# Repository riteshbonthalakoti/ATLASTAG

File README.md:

# AtlasTag

> **AtlasTag** is an ultra-compact, long-battery-life hardware asset-tracking platform combining GNSS satellite positioning, cellular IoT connectivity (LTE-M / NB-IoT), motion-triggered intelligence, and local fail-safe telemetry storage. Developed for **Hack Club Half Life**.

---

## Concept & Vision Reel

> [!NOTE]
> **Idea & Concept Showcase:** This video is an **idea reel / conceptual mockup** visualizing the intended asset-tracking experience, compact form-factor goals, and operational scenario for AtlasTag. It illustrates the project goals rather than physical bench-tested hardware (hardware design and subsystem validation are currently underway in Week 1).

https://github.com/user-attachments/assets/558ffe17-422e-43a5-9f9e-540db29d0795

---

## The Problem & The AtlasTag Approach

Most popular asset trackers (such as Apple AirTags or Tile) rely exclusively on crowd-sourced Bluetooth networks. When an asset leaves urban density or moves along transit highways, rural routes, or industrial yards without nearby smartphones, **tracking is lost**.

AtlasTag is engineered to operate **fully autonomously**:
- **Direct Satellite Positioning:** Acquires real-world geographic coordinates via multi-constellation GNSS (GPS, GLONASS, Galileo, BeiDou) without relying on external devices.
- **Direct Cellular Telemetry:** Transmits location packets directly to cloud servers over power-efficient LTE-M or NB-IoT networks.
- **Fail-Safe Offline Storage:** When traversing cellular dead zones or shielded containers, telemetry records are queued in local SPI NOR Flash memory and uploaded automatically once coverage is restored.
- **Ultra-Low Power Motion Gating:** Stays in deep micro-ampere sleep when stationary, waking up instantaneously via accelerometer interrupts when motion or tampering is detected.

---

## Visual Architecture & Data Flow

```mermaid
flowchart LR
    %% Main Pipeline
    Motion["🚶 Motion Sensor<br/><b>(Detects Movement)</b>"]
    -->|"1. Hardware Interrupt"| Brain["🧠 Host MCU / Controller<br/><b>(System Logic)</b>"]

    GPS["🛰️ GNSS Satellites<br/><b>(Latitude / Longitude)</b>"]
    -->|"2. Position Fix"| Brain

    Brain
    -->|"3. Formats Packet"| Modem["📶 Cellular Modem<br/><b>(LTE-M / NB-IoT)</b>"]

    Modem
    -->|"4. Cloud Uplink"| CloudApp["📱 Web / Mobile App<br/><b>(Live Map & Alerts)</b>"]

    %% Backup Storage
    Modem -.->|"No Signal (Offline)"| Storage["💾 SPI NOR Flash<br/><b>(Queues Telemetry)</b>"]
    Storage -.->|"Burst Upload on Reconnect"| Modem

    %% Power
    Power["🔋 Li-Po Battery & Charger<br/><b>(Power Management)</b>"]
    ==>|"Regulated 3.3V & VBAT Burst"| Brain

    %% Styling
    style Motion fill:#E8F5E9,stroke:#2E7D32,stroke-width:2px,color:#1B5E20
    style GPS fill:#E1F5FE,stroke:#0288D1,stroke-width:2px,color:#01579b
    style Brain fill:#EDE7F6,stroke:#512DA8,stroke-width:2px,color:#311B92
    style Modem fill:#FFF3E0,stroke:#E65100,stroke-width:2px,color:#BF360C
    style CloudApp fill:#FCE4EC,stroke:#C2185B,stroke-width:2px,color:#880E4F
    style Storage fill:#FFFDE7,stroke:#FBC02D,stroke-width:2px,color:#F57F17
    style Power fill:#ECEFF1,stroke:#455A64,stroke-width:2px,color:#263238
```

### The 5-Step Operating Cycle

1. **Deep Sleep Preservation:** Between tracking events, the system enters deep sleep, turning off RF radios to maximize battery longevity.
2. **Motion-Triggered Wakeup:** When vibration or acceleration exceeds the programmed threshold, the low-power accelerometer asserts a hardware interrupt pin to wake the host controller.
3. **Satellite GNSS Fix:** The GNSS receiver powers on, locks ephemeris data, and acquires high-accuracy geographic coordinates.
4. **Cellular Uplink:** The cellular engine establishes an LTE-M / NB-IoT network bearer and pushes the telemetry packet to the endpoint.
5. **Store-and-Forward Safety Net:** If no cellular tower acknowledges transmission, the packet is written to the on-board Winbond SPI Flash queue and forwarded during the next successful network attachment.

---

## Current Status: Week 1 Modular Baseboard

*AtlasTag Week 1 Modular Prototype Baseboard (45 × 35 mm, 4-Layer Controlled-Impedance Stackup).*

### Current Engineering State:
- **Schematic Capture Complete:** Authoritative baseboard schematic captured in KiCad 10.0.6 (`hardware/kicad/atlastag.kicad_sch`), passing electrical rules check (ERC) with zero critical errors.
- **Modular Mezzanine Architecture:** Implements a standardized 16-pin interface (VBAT, 3.3V, GND, UART, control GPIOs, SIM interface), keeping the Cellular/GNSS modem selection **open** and avoiding unverified fine-pitch BGA/LGA soldering risks.
- **Power Path Design:**
  - **USB-C Interface:** Mid-mount receptacle with dual 5.1 kΩ CC pull-downs for standard 5V supply negotiation.
  - **Battery Charger:** Microchip MCP73831 linear Li-Po charger with $R_{PROG} = 4.7\text{ k}\Omega$ setting a safe 212 mA charging current limit.
  - **System LDO:** Diodes Inc AP2112K-3.3 (600 mA, ultra-low dropout) supplying clean 3.3V power.
  - **Burst Current Reservoir:** Dedicated 100 µF 10V low-ESR ceramic capacitor on the VBAT rail to buffer RF transmission bursts.
- **Telemetry Queue Memory:** Winbond W25Q32JVSSIQ (32 Mb / 4 MB) SPI NOR Flash in an iron-solderable SOIC-8 package.
- **Motion Sensor Interface:** 5-pin 2.54 mm breakout header (3V3, GND, SCL, SDA, INT) for modular MEMS accelerometer integration.
- **Layout & Routing Status:** Preliminary 4-layer layout drafted (45 × 35 mm). Full internal plane copper pours, signal routing, and interactive KiCad DRC remain pending physical board completion. Fabrication outputs are currently marked **STRICTLY NOT FOR FABRICATION**.

---

## Hardware Architecture: Modular Baseboard + Mezzanine

To reconcile strict hand-assembly constraints (soldering iron only) with high-density cellular modules, AtlasTag separates the design into two distinct layers:

| Layer | Function | Primary Components | Assembly Method |
| :--- | :--- | :--- | :--- |
| **Baseboard (45 × 35 mm)** | Power management, charging, battery monitoring, offline flash, SIM interface, sensor header | MCP73831, AP2112K-3.3, Winbond W25Q32, Nano-SIM socket, USB-C | 100% Iron-Solderable (0603 passives, SOT-23-5, SOIC-8, through-hole headers) |
| **Carrier / Mezzanine** | Cellular connectivity (LTE-M/NB-IoT), GNSS receiver, RF front-end | Nordic nRF9151, Quectel BG95-M3, or SIMCom SIM7080G carrier | Pre-assembled SMT carrier or breakout connecting via 16-pin 2.54 mm header |

---

## Cellular / GNSS Platform Trade Study (Status: OPEN)

The primary modem platform decision remains **deliberately open** to ensure rigorous verification of network compatibility and hand-assembly feasibility:

| Candidate | Form Factor | Connectivity | Internal MCU | Assembly Assessment |
| :--- | :--- | :--- | :--- | :--- |
| **Nordic nRF9151** | Compact SiP (11×12 mm) | LTE-M / NB-IoT / GNSS | ARM Cortex-M33 (64 MHz, 1 MB Flash) | High density; requires pre-assembled mezzanine carrier for iron assembly. |
| **Quectel BG95-M3** | SMT Module (23.6×19.9 mm) | LTE-M / NB-IoT / EGPRS / GNSS | Requires external host MCU | Standard cellular module; requires carrier breakout or stencil reflow. |
| **SIMCom SIM7080G** | SMT Module (17.6×15.7 mm) | LTE-M / NB-IoT / GNSS | Requires external host MCU | Readily available development breakouts; low entry cost. |

> **Network Note:** Reliance Jio NB-IoT SIM provisioning and local band coverage in India remain **unverified** pending active carrier SIM acquisition and bench validation.

---

## Bill of Materials & Budget Compliance

AtlasTag is developed within the **Hack Club Half Life Tier 3 budget limit of $100.00 USD** (~₹9,670 INR at verified rate ₹96.70/USD).

| Subsystem | Cost (USD) | Cost (INR @ ₹96.70) | Notes |
| :--- | :--- | :--- | :--- |
| **Physical Baseboard Parts** | **$11.70** | **₹1,131.41** | All baseboard SMT components, charger, regulator, flash, SIM socket, headers |
| **Core System Projection** | **$44.25** | **₹4,278.98** | Baseboard + candidate cellular/GNSS engine + Li-Po cell + antennas |
| **Budget Headroom** | **+$55.75** | **+₹5,391.02** | Remaining contingency under the $100.00 USD Tier 3 grant limit |

Authoritative component details, manufacturer part numbers (MPNs), and distributor URLs are tracked in [`bom/BOM.md`](bom/BOM.md) and [`bom.csv`](bom.csv).

---

## Repository Structure

```text
ATLASTAG/
├── bom/                      # Authoritative detailed Bill of Materials (BOM.md, bom.csv)
├── docs/
│   ├── architecture/         # System architecture & hardware block diagrams
│   ├── decisions/            # Formal engineering trade study logs (DECISION_LOG.md)
│   ├── requirements/         # System requirements & project boundary gates
│   └── research/             # Component research, datasheets & network investigations
├── firmware/
│   └── src/                  # Architectural state machine stubs & driver development
├── hardware/
│   ├── gerbers/              # Fabrication files (Marked NOT FOR FABRICATION during draft)
│   └── kicad/                # KiCad 10 schematic (*.kicad_sch), PCB (*.kicad_pcb), netlist
└── README.md                 # Primary project documentation
```

---

## Development Workflow & Rules

- **Branch Model:** All active engineering occurs on branch `dev`. Stable milestones are promoted to `main` strictly through reviewed pull requests.
- **Truthful Engineering Integrity:** No subsystem is labeled as verified without bench testing, code implementation, and reproducible CLI reports.
- **Tooling:** KiCad 10.0.6 CLI automation, Git Conventional Commits (`feat:`, `fix:`, `docs:`, `chore:`).

---

## Hack Club Half Life

AtlasTag is an independent open-hardware development project created for the **Hack Club Half Life** hardware initiative.

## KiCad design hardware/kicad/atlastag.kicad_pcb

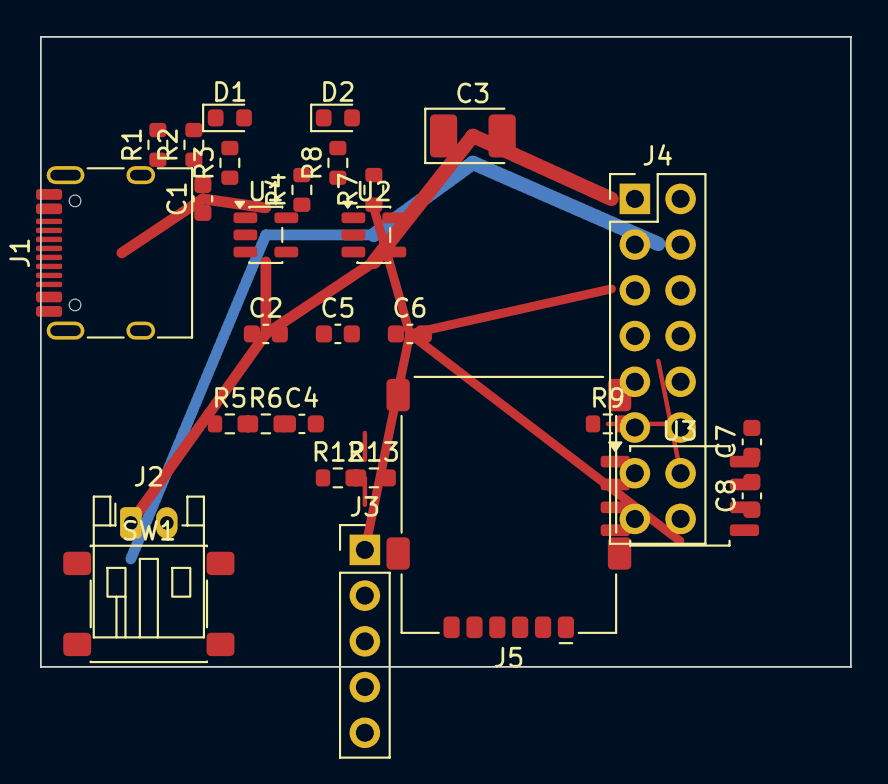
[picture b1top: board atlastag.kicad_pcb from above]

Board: 4 copper layers, 45.0 x 35.0 mm, 30 parts (0 on the bottom side), 4 nets.

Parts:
C1: 10uF VBUS; C_0603_1608Metric
C2: 10uF VBAT; C_0603_1608Metric
C3: 100uF Bulk; CP_EIA-3528-21_Kemet-B_HandSolder
C4: 10nF ADC; C_0603_1608Metric
C5: 4.7uF LDO_IN; C_0603_1608Metric
C6: 4.7uF LDO_OUT; C_0603_1608Metric
C7: 100nF Flash; C_0603_1608Metric
C8: 4.7uF Flash; C_0603_1608Metric
D1: Red CHG; LED_0603_1608Metric
D2: Green 3V3; LED_0603_1608Metric
J1: USB-C 5V In; USB_C_Receptacle_HRO_TYPE-C-31-M-12
J2: Li-Po Battery; JST_PH_S2B-PH-K_1x02_P2.00mm_Horizontal
J3: Motion Port; PinHeader_1x05_P2.54mm_Vertical
J4: Modem Mezzanine; PinHeader_2x08_P2.54mm_Vertical
J5: Nano-SIM; nanoSIM_GCT_SIM8060-6-0-14-00
R1: 5.1k CC1; R_0603_1608Metric
R2: 5.1k CC2; R_0603_1608Metric
R3: 1.5k LED; R_0603_1608Metric
R4: 4.7k PROG; R_0603_1608Metric
R5: 1.0M DIV_HI; R_0603_1608Metric
R6: 1.0M DIV_LO; R_0603_1608Metric
R7: 100k LDO_EN; R_0603_1608Metric
R8: 2.2k LED; R_0603_1608Metric
R9: 10k CS_PU; R_0603_1608Metric
R12: 4.7k SCL_PU; R_0603_1608Metric
R13: 4.7k SDA_PU; R_0603_1608Metric
SW1: User Button; SW_SPST_PTS645Sx43SMTR92
U1: MCP73831T; SOT-23-5
U2: AP2112K-3.3; SOT-23-5
U3: W25Q32JV; SOIC-8_5.3x5.3mm_P1.27mm

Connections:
+3V3: C6.1, C7.1, C8.1, J3.1, J4.5, U2.5, U3.3, U3.7, U3.8
GND: C1.2, C2.2, C3.2, C5.2, C6.2, C7.2, C8.2, J2.2, J3.2, J4.3, J4.4, U1.2, U1.5, U2.2, U3.4
VBAT: C2.1, C3.1, C5.1, J2.1, J4.1, J4.2, U1.3, U2.1, U2.3
VBUS: C1.1, U1.4
